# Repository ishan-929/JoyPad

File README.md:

# JoyPad
A custom MacroPad to suit your very needs.

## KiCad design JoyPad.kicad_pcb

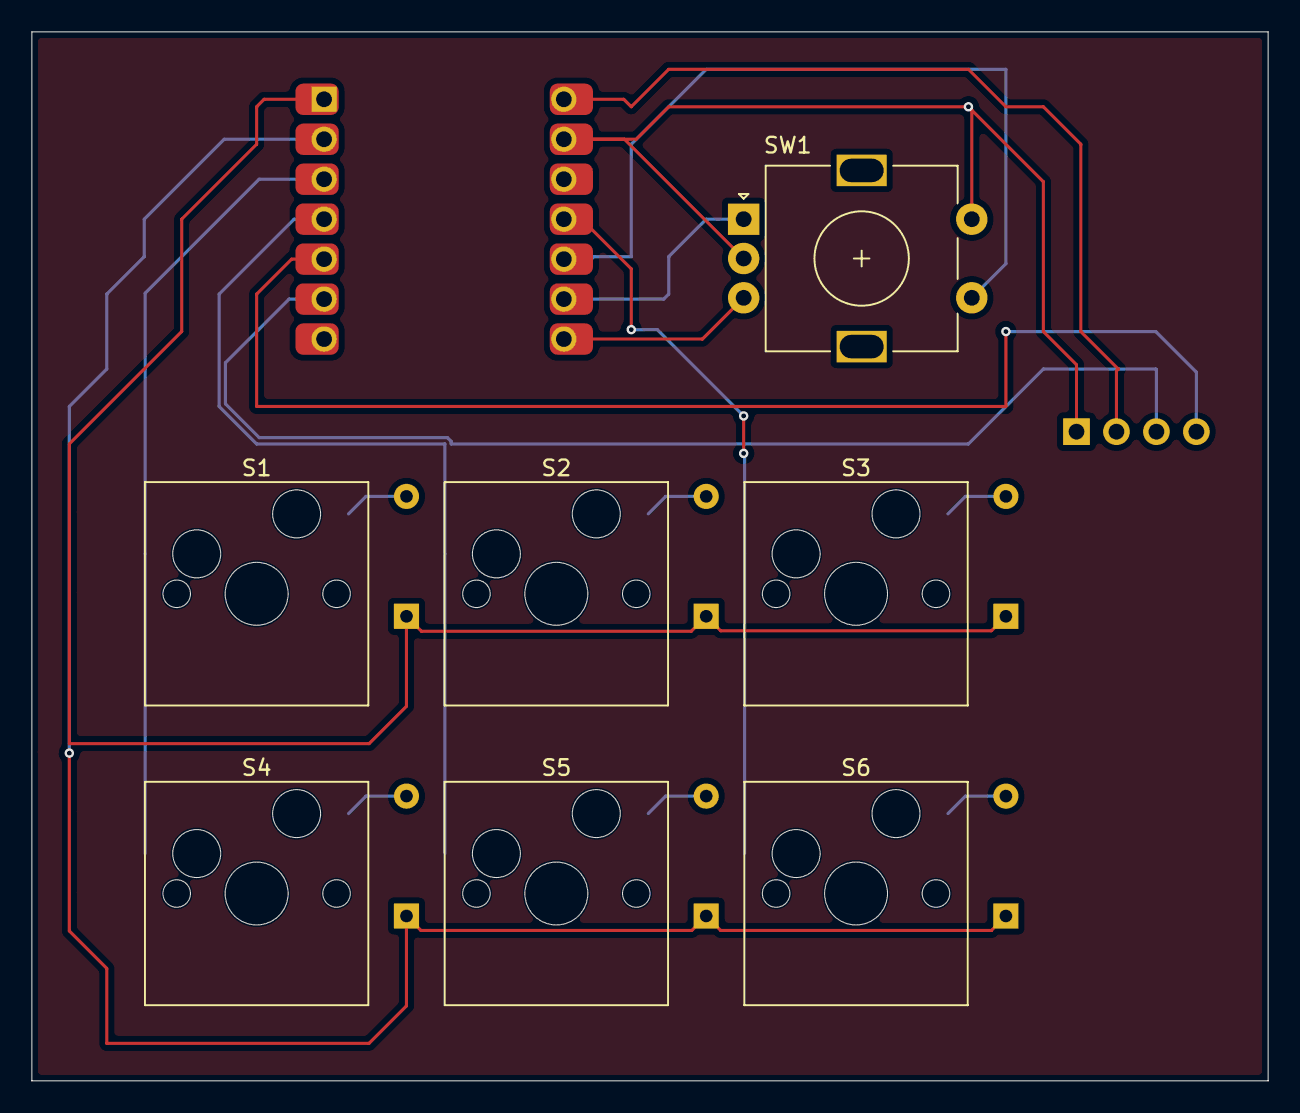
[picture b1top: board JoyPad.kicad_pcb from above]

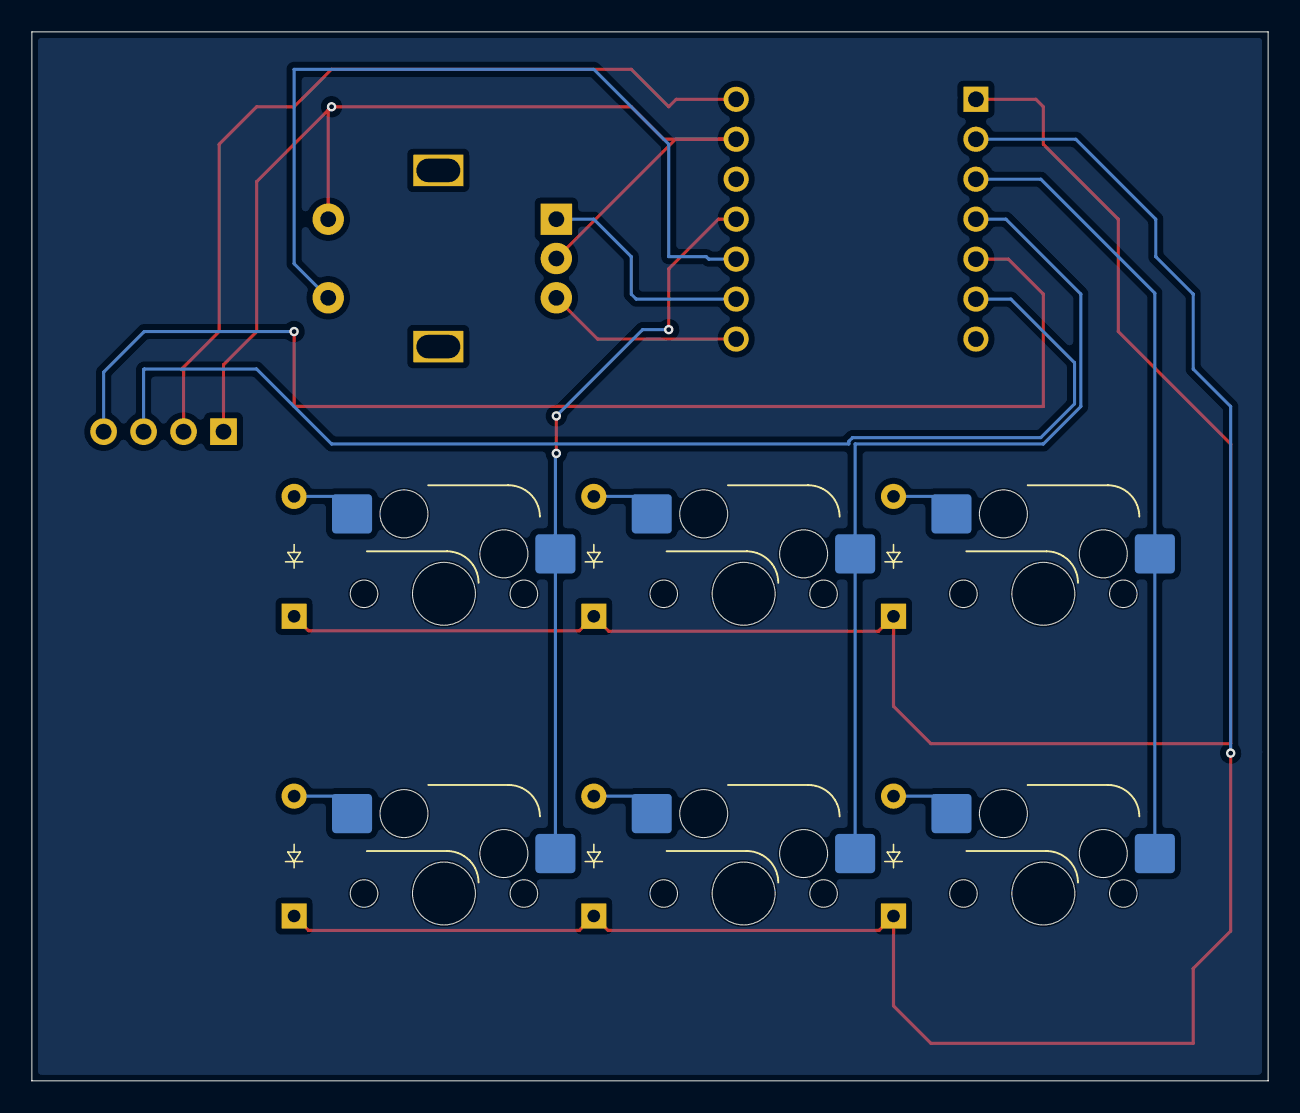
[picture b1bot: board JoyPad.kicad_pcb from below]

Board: 2 copper layers, 78.6 x 66.7 mm, 15 parts (6 on the bottom side), 18 nets.

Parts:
D1, D2, D3, D4, D5, D6: Diode_DO-35
J1: OLED_128x32
S1, S2, S3, S4, S5, S6: Hotswap_MX_1.00u
SW1: RotaryEncoder_Switch; RotaryEncoder_Alps_EC11E-Switch_Vertical_H20mm
U1: MCU_Seeed_XIAO_RP2040; Seeed_XIAO_RP2040

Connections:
5V: J1.2 (VCC), U1.14 (5V)
Col 0: S1.1, S4.1, U1.3 (PA10_A2_D2)
Col 1: S2.1, S5.1, U1.4 (PA11_A3_D3)
Col 2: S3.1, S6.1, U1.11 (PA6_A10_D10_MOSI)
D9: SW1.S1, U1.10 (PA5_A9_D9_MISO)
GND: J1.1 (GND), SW1.C, SW1.S2, U1.13 (GND)
unnamed: D1.2 (A), S1.2
unnamed: D2.2 (A), S2.2
unnamed: D3.2 (A), S3.2
unnamed: D4.2 (A), S4.2
unnamed: D5.2 (A), S5.2
unnamed: D6.2 (A), S6.2
RNA: SW1.A, U1.9 (PA7_A8_D8_SCK)
RNB: SW1.B, U1.8 (PB09_A7_D7_RX)
Row 0: D1.1 (K), D2.1 (K), D3.1 (K), U1.1 (PA02_A0_D0)
Row 1: D4.1 (K), D5.1 (K), D6.1 (K), U1.2 (PA4_A1_D1)
SCL: J1.3 (SCL), U1.6 (PA9_A5_D5_SCL)
SDA: J1.4 (SDA), U1.5 (PA8_A4_D4_SDA)

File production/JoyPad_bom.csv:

Designator,Footprint,Quantity,Value,LCSC Part #
"D1, D2, D3, D4, D5, D6",Diode_DO-35,6,~,
J1,OLED_128x32,1,OLED_128x32,
"S1, S2, S3, S4, S5, S6",Hotswap_MX_1.00u,6,~,
SW1,RotaryEncoder_Alps_EC11E-Switch_Vertical_H20mm,1,RotaryEncoder_Switch,
U1,Seeed_XIAO_RP2040,1,MCU_Seeed_XIAO_RP2040,
